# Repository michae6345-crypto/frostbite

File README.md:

# Frostbite

Frostbite is a 9-key macropad built around a Seeed XIAO RP2040, with a rotary encoder and a 128x32 I2C OLED. It shows
the status of my Claude Code sessions and ML training runs, and lets me act on them without switching windows.

The repo holds the KiCad PCB, a CadQuery case, QMK firmware in C, and a Python daemon that talks to the pad over raw
HID. Gerbers, case STEP/STL files and a compiled firmware image are in `production/`. The image above is a CAD render,
and nothing here documents a built or tested board yet.

## Hardware

- 2-layer PCB, 61.15 x 83.15 mm. The XIAO sits on the bottom side.
- 3x3 key matrix with 1N4148 diodes (COL2ROW), MX-style switches, an EC11E encoder and a 0.91" OLED.
- Printed case in four parts (Top, Bottom, OLEDSupport, Knob), 75.15 x 97.15 x 17.4 mm. Four M3x16 screws go into
  heat-set inserts in the Bottom. `CAD/frostbite_case.py` generates every case file.
- Parts list with sources and prices: [BOM.csv](BOM.csv).

## Firmware (C, QMK)

About 330 lines of C in `Firmware/`, most of it in `keymaps/default/keymap.c`.

The pad runs in one of two modes. With no host, it is a plain keyboard: the top six keys send F13-F18, the bottom row
sends F19, F20 and Escape, and the knob changes volume. Once the host daemon pings it, the pad switches to host mode.
Key presses become HID reports instead of keystrokes, with tap and hold (400 ms) told apart. The knob then picks one
of six slots. If no ping arrives for 5 s, the pad falls back to keyboard mode. Talk keeps sending F20 in both modes
so it works as a push-to-talk key.

The protocol uses 32-byte raw HID reports on usage page 0xFF60 (VID 0xFEED, PID 0x4642). Byte 0 is the command:

| Byte 0 | Direction | Meaning |
|---|---|---|
| 0x01 | host to pad | set one slot's status |
| 0x02 | host to pad | set all six statuses |
| 0x03 | host to pad | write a line of OLED text |
| 0x05 | both | ping, pad replies with protocol version and selected slot |
| 0x06 | host to pad | set the selected slot |
| 0x81 | pad to host | key event (index, tap or hold) |
| 0x82 | pad to host | encoder turn and new selected slot |

The OLED shows the selected slot, a summary line and a status letter for each of the six slots. It turns off after
10 minutes with no activity.

## Host software (Python)

About 2,650 lines in `host/frostbite_host/`, needing Python 3.12+ and `hidapi`.

- `frostbite-daemon` finds the pad by VID/PID and usage page, keeps slot state and pushes it to the OLED.
- `frostbite-hook` is a Claude Code hook ([host/claude-hooks.json](host/claude-hooks.json)). It reports session events
  to the daemon over a Unix socket. On a permission request it waits for Approve: a tap allows, a hold denies.
- `--watch-train PATH` tails a training log or JSONL file and reads epoch, step and loss from it.
- `frostbite-ctl` sets, clears and selects slots by hand, adds log watches, and prints the hooks config.

Tapping a session key selects it and focuses its terminal. Stop sends Escape to the selected session, but only when its terminal is in front. Both use `osascript`, so they only
work on macOS.

## Wiring and build

Pin map (from `Firmware/readme.md`, matching `keyboard.json` and `config.h`):

| XIAO | GPIO | Net |
|---|---|---|
| D0 | GP26 | ROW0 |
| D1 | GP27 | ROW1 |
| D2 | GP28 | ROW2 |
| D3 | GP29 | COL0 |
| D9 | GP4 | COL1 |
| D10 | GP3 | COL2 |
| D4 | GP6 | OLED SDA (I2C1, address 0x3C) |
| D5 | GP7 | OLED SCL |
| D7 | GP1 | ENC_A |
| D8 | GP2 | ENC_B |

Build the firmware with a working [QMK](https://docs.qmk.fm/) setup:

```sh
cd Firmware
ln -s "$PWD" ~/qmk_firmware/keyboards/frostbite
qmk compile -kb frostbite -km default
```

To reach the RP2040 bootloader, double-tap reset on the XIAO or hold Approve while plugging it in. A prebuilt
image is at `production/firmware.uf2`.

Run the host from the repo root:

```sh
uv tool install ./host
frostbite-daemon                 # or: frostbite-daemon --fake (simulated pad, type commands on stdin)
frostbite-ctl hooks --hook "$(which frostbite-hook)"   # paste the output into ~/.claude/settings.json
```

## Repo layout

```
PCB/          KiCad schematic, board and footprints
CAD/          CadQuery case script and full assembly STEP
Firmware/     QMK keyboard: keyboard.json, config.h, keymap.c
host/         Python daemon, Claude Code hook and CLI
production/   gerbers, case STEP/STL, firmware.uf2
assets/       renders and schematic image
BOM.csv       parts, sources, prices
```

## Credits

The layout is based on [Stratum](https://github.com/ReuTheCoder/stratum-macropad). Everything except the PCB and the
printed case comes from the Hack Club Hackpad kit. I used Claude Code to help build this project.

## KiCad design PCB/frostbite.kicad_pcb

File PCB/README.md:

# Frostbite 9 PCB

KiCad 10 project. Open `frostbite.kicad_pro`.

The board has 9 MX keys, an EC11E encoder, a 0.91" I2C OLED and a Seeed XIAO RP2040 on the underside. It has two layers and measures 61.15 x 83.15 mm.

Plots: [front](images/pcb_front.png), [back, mirrored](images/pcb_back.png).

| | |
|---|---|
|  |  |
|  |  |

## Regenerate

Everything comes from `../design.json`. Nothing is placed by hand. Run `sh PCB/tools/build_all.sh`. It does these steps:

1. `make_libs.py` writes the derived footprint, the lib tables and the project settings. Net classes are Default (0.25 mm) and Power (0.5 mm, for GND and +3V3). Clearance is 0.2 mm.
2. `gen_schematic.py` writes the schematic, then ERC runs. UUIDs are deterministic, so the PCB stays linked across runs.
3. `check_netlist.py` works out every net from `design.json`, then checks the exported netlist and `keyboard.json` against it.
4. `gen_pcb.py place` adds the outline, footprints, nets and silkscreen, and writes the Specctra DSN. It needs KiCad's bundled Python.
5. `gen_pcb.py route` runs Freerouting 2.5.0 headless, with the DSN clearance raised to 0.3 mm to stay clear of the board edge. Neck-downs go back to 0.2 mm, then the GND pours are added.
6. DRC runs with schematic parity.
7. `export_bottom_pads.py` writes `build/bottom_pads.json` for the case checks.
8. The script exports Gerbers, drill files, the pos file, `production/gerbers.zip` and the images.

`frostbite.kicad_dru` holds the JLCPCB 2-layer 1 oz rules from `verify/rules/`. The PTH annular ring is raised from 0.18 to JLCPCB's published 0.20.

`gerbers.zip` has F/B Cu, Mask, Paste, Silkscreen and Edge.Cuts with Protel names, silk clipped at the mask, PTH and NPTH Excellon drill files, and a job file.

Last results with KiCad 10.0.8:

* ERC: 0 violations.
* DRC: 0 errors, 0 unconnected, 0 parity issues. At all severities there are 25 warnings, all from the care-package XIAO silk.
* Netlist: 0 differences (21 named nets, 56 pins, 21 parts).
* Freerouting: 0 unrouted, 126 track segments, 3 vias.

## Footprints

* The XIAO symbol and `XIAO-Generic-Hybrid-14P-2.54-21X17.8MM` come from the care package, `github.com/hackclub/hackpad`, `extras/kicad_care_package/`, at `clean` `fb6f7d2cd5d704b01ff011619e0581c751318d15`.
* `MX-Solderable-1U` comes from the same path at `main` `ff97fbd16f7aa6db5860ee1d027b3caf95594599`.
* Diodes and J1 are KiCad standard: `D_DO-35_SOD27_P7.62mm_Horizontal` and `PinHeader_1x04_P2.54mm_Vertical`.
* `lib/frostbite.pretty/EC11E-Switch_Vertical_H20mm_Slot3.4x1.5` is KiCad's slotted EC11E with 3.4 x 1.5 lug slots and 4.0 x 2.1 pads.

## Assembly

Solder the XIAO to the underside at `XIAO HERE`, with its components facing away from the PCB. Fit the switches, diodes, encoder and J1 from the top.

## Placement

PCB coordinates are in mm, with the origin at the top left and y pointing down. `kicad-cli pcb export pos` negates y. ENC1's origin is pad A (46.65, 20.5). J1's origin is pin 1.

| ref | where | position |
|---|---|---|
| SW1 to SW9 | top | switch centres at `design.json keys[]` |
| D1 to D9 | top, vertical in the 5 mm gap right of each switch | (x + 9.525, y), anode up, cathode (K, square pad) at y + 3.81 |
| U1 | bottom (flipped), USB-C toward y = 0 | rect x 12.1 to 29.9, y 0 to 21.0, centre (21.0, 10.5) |
| ENC1 | top, rotated 90 degrees so the A/C/B row faces the keys, clear of J1 | shaft (49.15, 13.0); A/C/B at y 20.5 (x 46.65, 49.15, 51.65); S1/S2 at y 6.0; lugs (43.55, 13.0) and (54.75, 13.0) |
| J1 | top | pin row x 39.0; pins 1 to 4 at y 9.19, 11.73, 14.27, 16.81 = GND, VCC, SCL, SDA |

## GND pours

The XIAO's back sits on this board. It has bare VIN, GND, SWCLK, SWDIO and RST pads, plus USB shell tabs.

* Rule area `xiao_back` (x 15.4 to 26.6, y 0.4 to 21) keeps B.Cu tracks and vias out.
* `xiao_vin_gnd` (x 18.5 to 23.3, y 17.5 to 20.65) also clears the pour.
* `xiao_swd_rst` (x 18.7 to 23.3, y 0.7 to 5.5) also clears the pour.

Pad positions are scaled from Seeed's render (+/- 0.3 mm). The rest of the pour stays. It is GND, and solder mask insulates it.

Pours on both layers use thermal relief on every pad (gap 0.3, spoke 0.4). `min_resolved_spokes` is KiCad's default of 2.

## Encoder lugs

The lug is 2.5 mm wide with a barb tip 6.55 mm from the shaft. KiCad's 2.8 x 1.5 slot at +/-5.6 fails JLCPCB's 2:1 slot rule, and the barb must flex 0.50 mm at the lug corners.

This board's 3.4 x 1.5 slot at +/-5.6 passes at 2.27:1. The flex is 0.20 mm at the centre and 0.26 mm at the corners. Width and centre match KiCad's slot, so the barb still catches the outer edge. The extra length adds no play across the lug.

These figures come from Alps' STEP model. A kit clone may differ.

## OLED pin order

Take the common 0.91" 128x32 module, display side up, with the header at the right end. It presents GND, VCC, SCL, SDA from the back edge to the front edge. A vendor photo and the gorbachev footprint linked from the Hackpad guide agree, so J1 matches `design.json`.

Some clones swap GND and VCC. Compare the kit module's labels with the `GND VCC SCL SDA` silkscreen beside J1 before soldering. The silkscreen is on both faces.

## Nets

| net | |
|---|---|
| ROW0, ROW1, ROW2 | XIAO D0, D1, D2 (GP26, GP27, GP28) to the cathodes of D1-3, D4-6, D7-9 |
| COL0, COL1, COL2 | XIAO D3 (GP29), D9 (GP4), D10 (GP3) to pin 1 of the switches in column 0, 1, 2 |
| SW1_D to SW9_D | switch pin 2 to its 1N4148 anode (COL2ROW) |
| SDA, SCL | XIAO D4 (GP6), D5 (GP7) to J1 pin 4, pin 3 (I2C1; the module has its own pull-ups) |
| ENC_A, ENC_B | XIAO D7 (GP1), D8 (GP2) to encoder A, B |
| GND | XIAO GND, J1 pin 1, encoder C and lugs, both pours |
| +3V3 | XIAO 3V3 to J1 pin 2 (OLED VCC) |

Not connected: XIAO D6, XIAO 5V, and the encoder push switch (S1, S2).

## For the case

* Bottom side: the XIAO is about 3.5 mm tall (allow `xiaoDetail.tMax` 4.5 + 0.5). THT lead ends reach about 1.7 to 2 mm.
* USB-C: the receptacle is centred at x = 21.0, 9.0 wide, on the underside. It overhangs y = 0 by 1.42 mm per Seeed's footprint. Seeed's STEP gives 1.0, and the case fits either. The XIAO board edge is flush with y = 0.
* Top side: only the diodes (2 mm diameter, under the plate), J1 and ENC1. The OLED outline (x 2.5 to 40.5, y 7 to 19) is free of parts apart from flush XIAO pads.
* There are no mounting holes. `design.json` puts the M3 inserts in the bezel, outside the PCB.

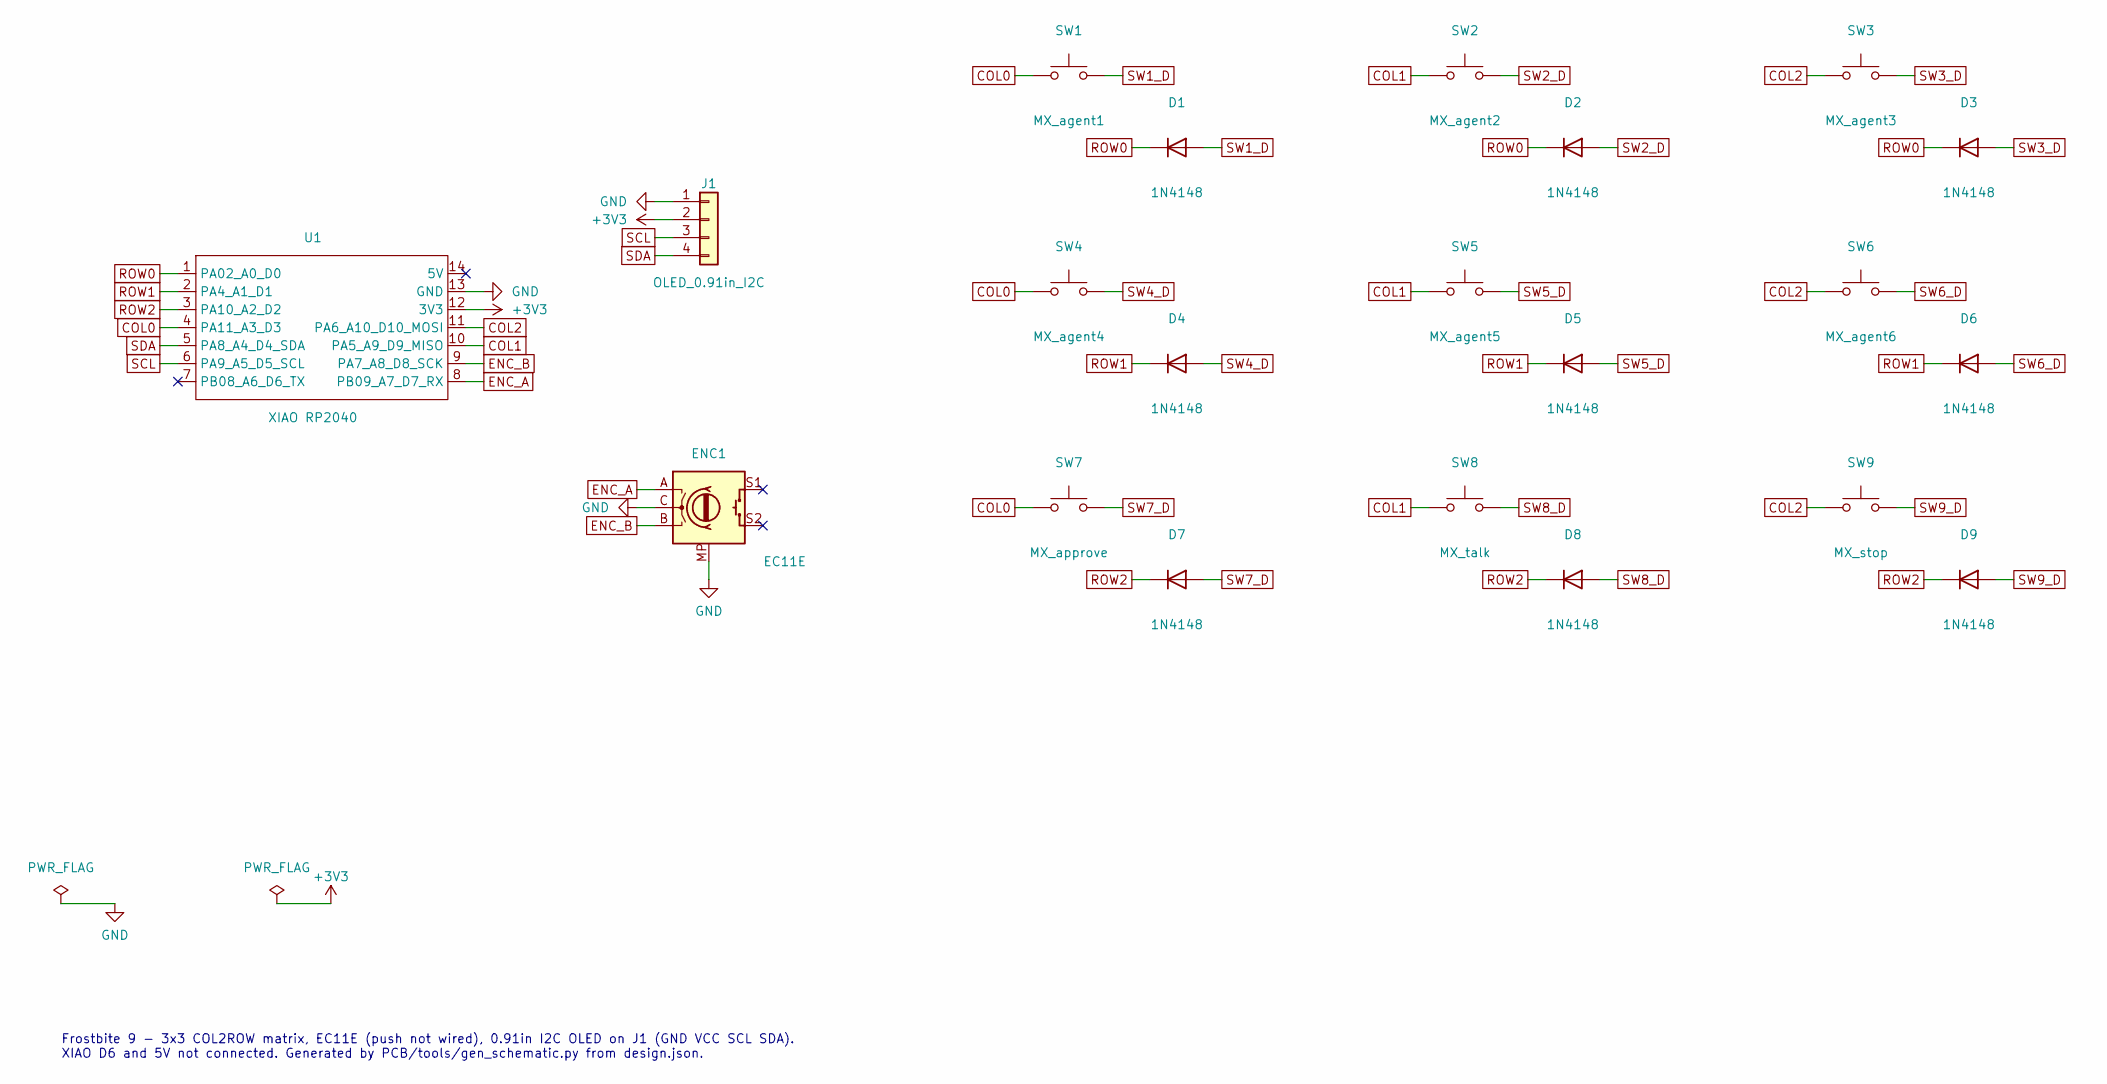
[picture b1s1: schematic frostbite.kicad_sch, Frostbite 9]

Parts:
D1, D2, D3, D4, D5, D6, D7, D8, D9: 1N4148; D_DO-35_SOD27_P7.62mm_Horizontal
ENC1: EC11E; EC11E-Switch_Vertical_H20mm_Slot3.4x1.5
J1: OLED_0.91in_I2C; PinHeader_1x04_P2.54mm_Vertical
SW1: MX_agent1; MX-Solderable-1U
SW2: MX_agent2; MX-Solderable-1U
SW3: MX_agent3; MX-Solderable-1U
SW4: MX_agent4; MX-Solderable-1U
SW5: MX_agent5; MX-Solderable-1U
SW6: MX_agent6; MX-Solderable-1U
SW7: MX_approve; MX-Solderable-1U
SW8: MX_talk; MX-Solderable-1U
SW9: MX_stop; MX-Solderable-1U
U1: XIAO RP2040; XIAO-Generic-Hybrid-14P-2.54-21X17.8MM

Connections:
+3V3: J1.2, U1.12 (3V3)
COL0: SW1.1, SW4.1, SW7.1, U1.4 (PA11_A3_D3)
COL1: SW2.1, SW5.1, SW8.1, U1.10 (PA5_A9_D9_MISO)
COL2: SW3.1, SW6.1, SW9.1, U1.11 (PA6_A10_D10_MOSI)
ENC_A: ENC1.A, U1.8 (PB09_A7_D7_RX)
ENC_B: ENC1.B, U1.9 (PA7_A8_D8_SCK)
GND: ENC1.C, ENC1.MP, J1.1, U1.13 (GND)
ROW0: D1.1 (K), D2.1 (K), D3.1 (K), U1.1 (PA02_A0_D0)
ROW1: D4.1 (K), D5.1 (K), D6.1 (K), U1.2 (PA4_A1_D1)
ROW2: D7.1 (K), D8.1 (K), D9.1 (K), U1.3 (PA10_A2_D2)
SCL: J1.3, U1.6 (PA9_A5_D5_SCL)
SDA: J1.4, U1.5 (PA8_A4_D4_SDA)
SW1_D: D1.2 (A), SW1.2
SW2_D: D2.2 (A), SW2.2
SW3_D: D3.2 (A), SW3.2
SW4_D: D4.2 (A), SW4.2
SW5_D: D5.2 (A), SW5.2
SW6_D: D6.2 (A), SW6.2
SW7_D: D7.2 (A), SW7.2
SW8_D: D8.2 (A), SW8.2
SW9_D: D9.2 (A), SW9.2

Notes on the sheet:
Frostbite 9 - 3x3 COL2ROW matrix, EC11E (push not wired), 0.91in I2C OLED on J1 (GND VCC SCL SDA). XIAO D6 and 5V not connected. Generated by PCB/tools/gen_schematic.py from design.json.

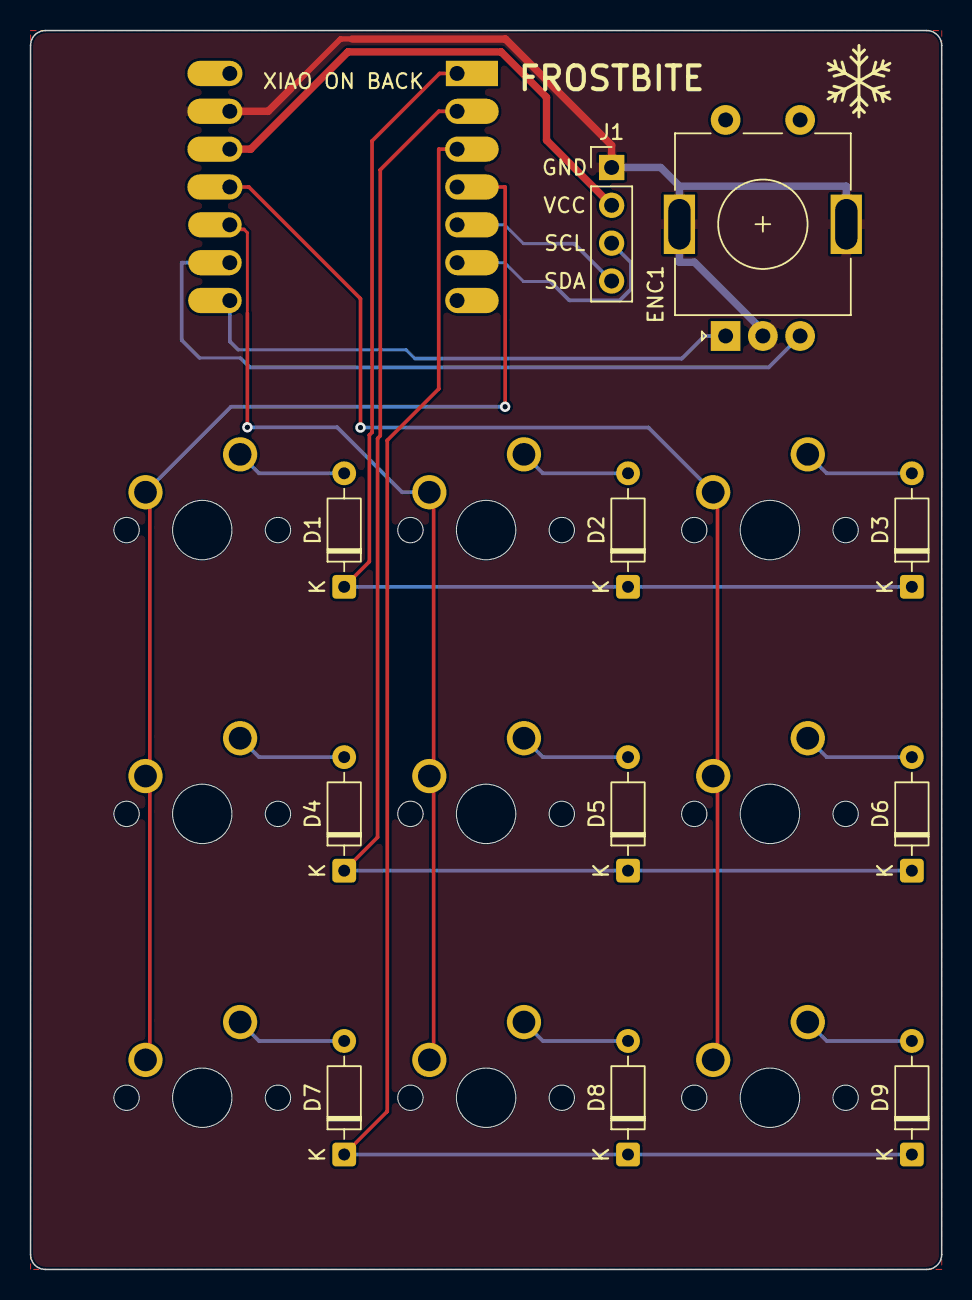
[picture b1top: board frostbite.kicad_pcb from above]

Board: 2 copper layers, 61.1 x 83.2 mm, 21 parts (1 on the bottom side), 21 nets.
